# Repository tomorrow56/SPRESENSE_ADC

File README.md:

# SPRESENSE_ADC
Grove ADC expansion board for SPRESENSE

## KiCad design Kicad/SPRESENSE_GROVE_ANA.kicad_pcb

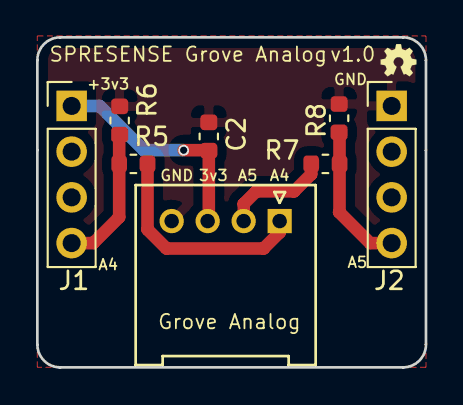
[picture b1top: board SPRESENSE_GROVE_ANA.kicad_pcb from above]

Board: 2 copper layers, 21.6 x 18.3 mm, 9 parts (0 on the bottom side), 6 nets.

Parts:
C2: 10uF; C_0603_1608Metric
Grove Analog: Conn_01x04; Grove_4x2.00mm_Angle
J1, J2: JP1; PinHeader_1x04_P2.54mm_Vertical
LOGO1: OPEN_HARDWARE_1; OSHW-logo_silkscreen-front_2mm
R5, R7: 39k; R_0603_1608Metric
R6, R8: 10k; R_0603_1608Metric

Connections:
+3V3: C2.1, Grove Analog.3, J1.1
/AIN4: J1.4, R5.1, R6.2
/AIN5: J2.4, R7.2, R8.2
A4: Grove Analog.1, R5.2
A5: Grove Analog.2, R7.1
GND: C2.2, Grove Analog.4, J2.1, R6.1, R8.1

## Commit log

2020-06-07 Input error correction function added
